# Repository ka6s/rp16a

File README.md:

# rp16a
This is version 1.3 of the rp16a Red Pitaya Shield.  This is an enhancment over the rp_adapter in several ways.  The design adds 10db and 20db attenuation. It has interfaces for both Alex filtering and 4 bit bus control for OTHER external filters.  It provides control for a 3 antenna switch.   The design uses a single 12V supply and mounts the Red Pitaya underneath the shield. 

Also contained within this repository are the following:
sdr-transceiver-hpsdr.c - custom version of Pavel's code to use with this radio.  
cc - compiler command to compile the above.
RP_i2c_to_SPI_v2.tar.gz - PSoC Creator 4.4 tar ball for the on-board PSOC that provides antenna control and translation for Alex.

If you aren't going to use Alex -and only 1 antenna - then you don't need any of these files.

Steve KA6S

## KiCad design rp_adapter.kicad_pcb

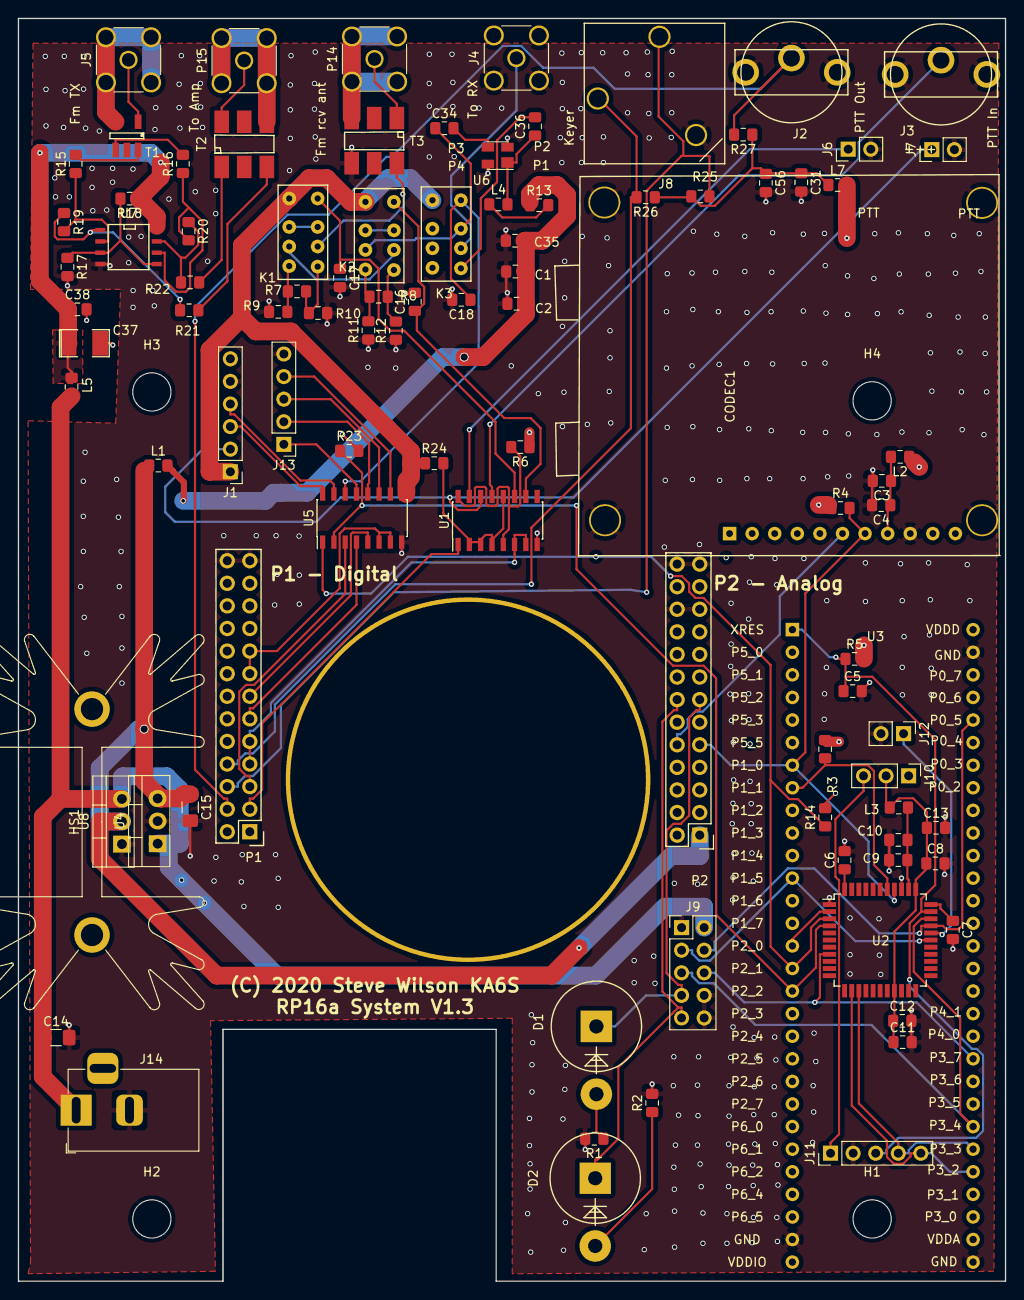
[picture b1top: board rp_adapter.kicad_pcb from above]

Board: 4 copper layers, 111.0 x 142.0 mm, 99 parts (1 on the bottom side), 86 nets.

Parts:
C1: 0.1 uF; C_0805_2012Metric_Pad1.15x1.40mm_HandSolder
C2: 0.001uF; C_0805_2012Metric_Pad1.15x1.40mm_HandSolder
C3, C5, C10, C11, C13, C16, C17, C18, C31, C34, C35, C36, C38: 0.1uF; C_0805_2012Metric_Pad1.15x1.40mm_HandSolder
C4, C6, C7, C8, C9, C12, C56: 1uF; C_0805_2012Metric_Pad1.15x1.40mm_HandSolder
C14, C15: 10uF; C_1206_3216Metric_Pad1.42x1.75mm_HandSolder
C37: 10uF; SMD-1210_Pol
CODEC1: Conn_01x11; CODEC
D1, D2: ZENER; Diode_P600_Vertical_AnodeUp
H1, H2, H3, H4: MountingHole; MountingHole_4.3mm_M4
HS1: Heatsink; Heatsink_Fischer_SK129-STS_42x25mm_2xDrill2.5mm
J1: Conn_01x06; PinHeader_1x06_P2.54mm_Vertical
J2, J3: Conn_Coaxial; RCAVertical
J4, J5: SMA; SMA_Amphenol_132291-12_Vertical
J6, J7: Conn_01x02; PinHeader_1x02_P2.54mm_Vertical
J8: AudioJack2_Ground; Audio_3P_Vertical
J9: Conn_02x05_Odd_Even; PinHeader_2x05_P2.54mm_Vertical
J10: Conn_01x03_Male; PinHeader_1x03_P2.54mm_Vertical
J11: Conn_01x05_Male; PinHeader_1x05_P2.54mm_Vertical
J12: Conn_01x02_Male; PinHeader_1x02_P2.54mm_Vertical
J13: Conn_01x05; PinHeader_1x05_P2.54mm_Vertical
J14: Barrel_Jack_MountingPin; BarrelJack_Horizontal
K1, K2, K3: RELAY_RF; G6J-2P-Y
L1, L2, L3, L4, L5, L7: FB; L_0805_2012Metric_Pad1.15x1.40mm_HandSolder
MT1: 1pin; 1Pin
P1, P2: CONN_02X13; Pin_Header_Straight_2x13
P14, P15: SMA; SMA_Amphenol_132291-12_Vertical
R1, R2, R17, R18, R24: 1K; R_0805_2012Metric_Pad1.15x1.40mm_HandSolder
R3, R4: 10K; R_0805_2012Metric_Pad1.15x1.40mm_HandSolder
R5, R25, R26, R27: 4.7K; R_0805_2012Metric_Pad1.15x1.40mm_HandSolder
R6, R14, R23: 200; R_0805_2012Metric_Pad1.15x1.40mm_HandSolder
R7, R13: 75; R_0805_2012Metric_Pad1.15x1.40mm_HandSolder
R8: 240; R_0805_2012Metric_Pad1.15x1.40mm_HandSolder
R9, R10, R15, R16: 100; R_0805_2012Metric_Pad1.15x1.40mm_HandSolder
R11, R12: 62; R_0805_2012Metric_Pad1.15x1.40mm_HandSolder
R19, R20: 5.1K; R_0805_2012Metric_Pad1.15x1.40mm_HandSolder
R21, R22: 4R99; R_0805_2012Metric_Pad1.15x1.40mm_HandSolder
T1: TC4-1T
T2: ADT1.5-1
T3: ADT1-1; ADT1.5-1
U1, U5: ULN2003; SOIC-16_3.9x9.9mm_P1.27mm
U2: CY8C4127AXI-S443; TQFP-44_10x10mm_P0.8mm
U3: CY8CKIT-43
U4: LM7805; TO-220-3_Vertical
U6: MAX2611; SOT-143
U7: OPA26741D; SOIC-8-N
U8: LM1085-5; TO-220-3_Vertical

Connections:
+12V: C14.1, J1.1, J9.2, J14.1, K1.1, K2.1, K3.1, L5.2, R24.1, U4.1, U5.9, U8.3
/ADCDAT: CODEC1.2, P1.14
/BCLK: CODEC1.1, P1.12
/DACDAT: CODEC1.3, P1.16
/I2C to SPI/RESET: C5.1, J11.3, R5.1, U2.32, U3.1
/I2C to SPI/RP_3.3V: J10.1, L2.1, L7.2, P1.1, P1.2, R3.1, R4.1, R5.2, R6.1, R14.2, R23.2, U3.29, U3.31, U3.58
/I2C to SPI/SAR_BYPASS: C6.1, U2.44
/I2C to SPI/SPI_RSTB: J9.5, U2.31, U3.36
/I2C to SPI/SPI_SCK: J9.4, U2.30, U3.54
/I2C to SPI/SPI_SDO: J9.3, U2.28, U3.12
/I2C to SPI/SPI_TSTB: J9.6, U2.8, U3.39
/I2C to SPI/SWDCLK: J11.4, U2.14, U3.35
/I2C to SPI/SWDIO: J11.5, U2.13, U3.34
/I2C to SPI/SWR_F: D1.1, J9.7, P2.13
/I2C to SPI/SWR_R: D2.1, J9.9, P2.14
/I2C to SPI/UART_TX: J12.1, U2.29
/I2C to SPI/VCCD: C7.1, U2.33
/I2C to SPI/VDDA: C9.1, C10.1, L3.1, U2.35
/I2C to SPI/VDDD: C8.1, C11.1, C12.1, C13.1, J10.2, L3.2, U2.19, U2.34
/I2C to SPI/VTARG: J10.3, J11.1
/I2C to SPI/ant1: U2.2, U3.15
/I2C to SPI/ant2: R14.1, U2.3, U3.16, U5.1
/I2C to SPI/ant3: R23.1, U2.4, U3.17, U5.2
/LRCLK: CODEC1.4, P1.18
/PTT_OUT: P1.3, U1.1
/SCLK: CODEC1.7, P2.9, R4.2, U2.37, U3.7
/SDAT: CODEC1.6, P2.10, R3.2, U2.38, U3.8
/db10: P1.7, P1.9, U1.6, U1.7
/extern_conn/3P3V_AUD: C31.1, C56.1, L7.1, R25.1, R26.1, R27.1
/extern_conn/DASH: J8.R, P1.6, R25.2
/extern_conn/DOT: J8.T, P1.8, R26.2
/extern_conn/PTT_IN: J2.1, P1.4, R27.2
/extern_conn/db10_n: C17.1, K1.8, U1.11
/extern_conn/db20_n: C16.1, K2.8, U1.10
/extern_conn/preamp_n: C18.1, K3.8, U5.14
/h1: P1.11, U5.4
/h2: P1.13, U5.5
/h3: P1.15, P1.17, U5.6, U5.7
/lna/5V_LNA: C1.1, C2.1, C35.1, L1.2, R13.1
/mini_amp/AMP12V: C37.1, C38.1, L5.1, R18.1, U7.8
/preamp: P1.5, U5.3
/ps/RP_5V: C15.1, L1.1, P2.1, U4.3, U8.2
Earth: J5.2, T1.4
GND: C1.2, C2.2, C3.2, C4.2, C5.2, C6.2, C7.2, C8.2, C9.2, C10.2, C11.2, C12.2, C13.2, C14.2, C15.2, C16.2, C17.2, C18.2, C31.2, C35.2, C37.2, C38.2, C56.2, CODEC1.9, J1.5, J2.2, J3.2, J4.2, J6.2, J7.2, J8.S, J9.1, J9.8, J9.10, J11.2, J12.2, J13.5, J14.2, P1.25, P1.26, P2.21, P2.22, P2.25, P2.26, R1.2, R2.2, R9.1, R10.1, R11.1, R12.1, R17.2, T3.4, U1.8, U2.1, U2.36, U3.28, U3.30, U3.57, U4.2, U5.8, U6.2, U6.4, U7.4, U8.1
GNDPWR: P15.2, T2.4
GNDREF: P14.2, T3.3
unnamed: C3.1, C4.1, CODEC1.8, L2.2
unnamed: C34.1, K2.3, K3.7
unnamed: C34.2, U6.3
unnamed: C36.1, L4.2, U6.1
unnamed: C36.2, K3.5
unnamed: D1.2, R1.1
unnamed: D2.2, R2.1
unnamed: J1.2, J7.1, U1.14
unnamed: J1.3, U5.16
unnamed: J1.4, U5.15
unnamed: J3.1, U1.13
unnamed: J4.1, K3.6
unnamed: J5.1, T1.6
unnamed: J6.1, U1.15
unnamed: J13.1, U5.13
unnamed: J13.2, U5.12
unnamed: J13.3, U5.11
unnamed: J13.4, U5.10
unnamed: K1.2, K1.7
unnamed: K1.3, K2.6
unnamed: K1.4, R7.1, R9.2
unnamed: K1.5, R7.2, R10.2
unnamed: K1.6, T3.6
unnamed: K2.2, K2.7
unnamed: K2.4, R8.1, R11.2
unnamed: K2.5, R8.2, R12.2
unnamed: L4.1, R13.2
unnamed: P14.1, T3.1
unnamed: P15.1, T2.6
unnamed: R6.2, U1.5, U1.16
unnamed: R15.1, R19.2, U7.2
unnamed: R15.2, T1.1
unnamed: R16.1, R20.2, U7.6
unnamed: R16.2, T1.3
unnamed: R17.1, R18.2, U7.3, U7.5
unnamed: R19.1, R21.1, U7.1
unnamed: R20.1, R22.2, U7.7
unnamed: R21.2, T2.3
unnamed: R22.1, T2.1
unnamed: R24.2, U1.2, U1.3, U1.4, U1.12

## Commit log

2021-12-29 Initial Release
2021-12-29 Add RP code and update Readme.

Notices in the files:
rp_adapter.kicad_pcb:
(C) 2020 Steve Wilson KA6S
